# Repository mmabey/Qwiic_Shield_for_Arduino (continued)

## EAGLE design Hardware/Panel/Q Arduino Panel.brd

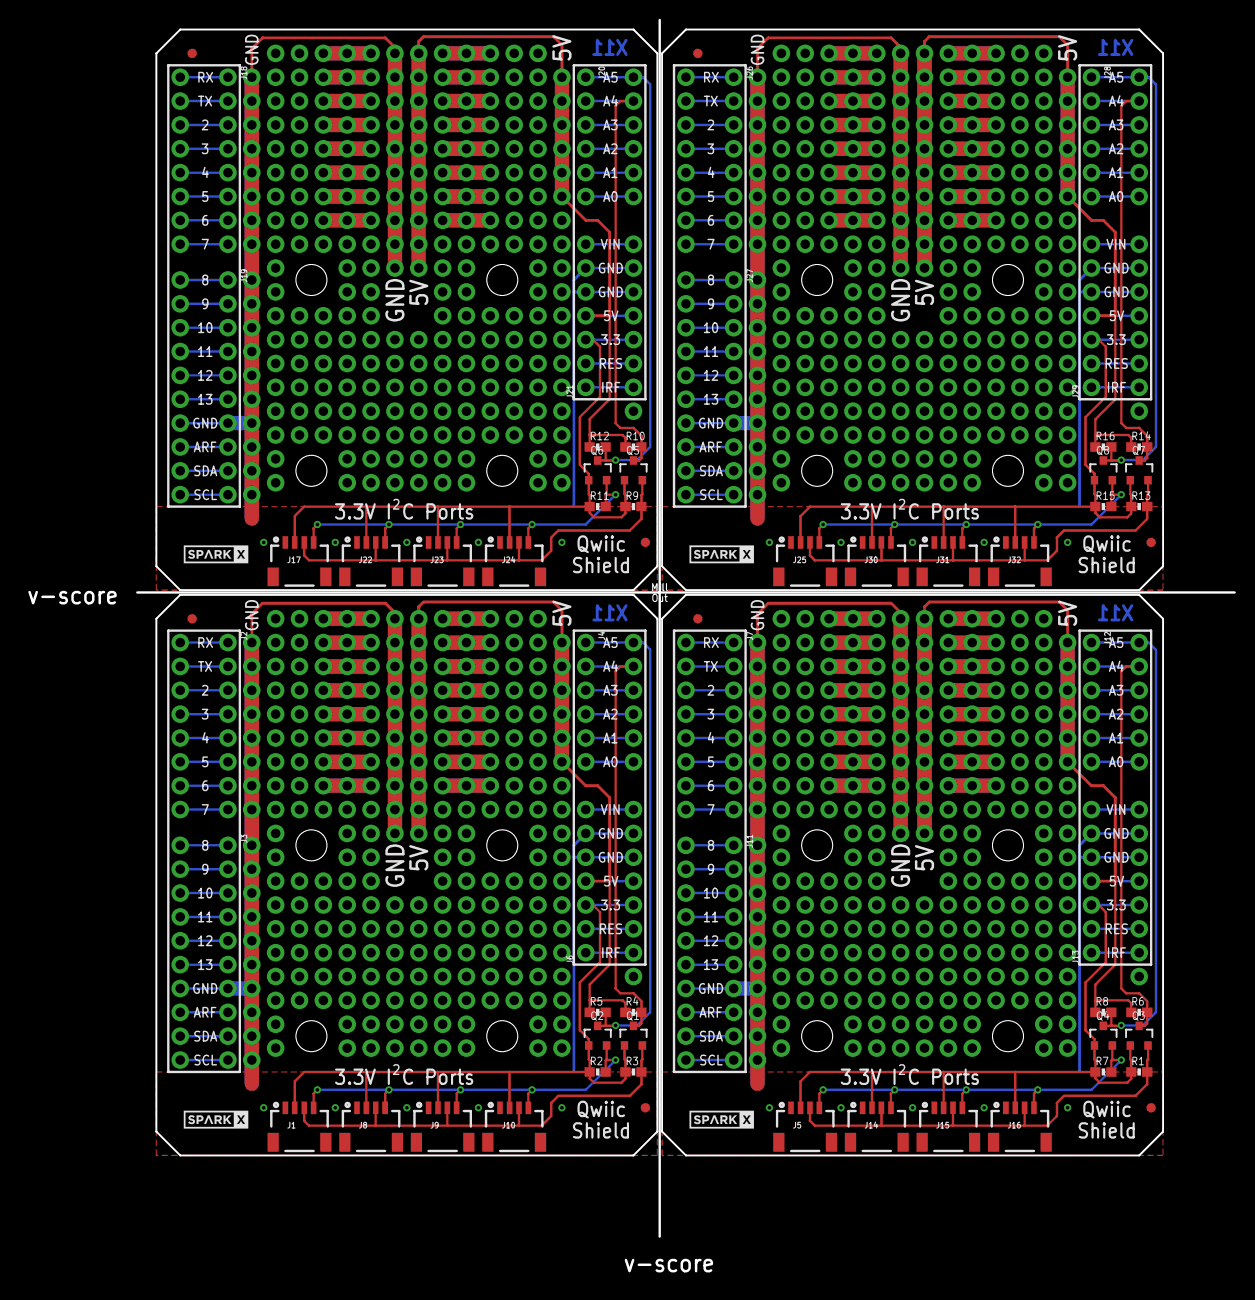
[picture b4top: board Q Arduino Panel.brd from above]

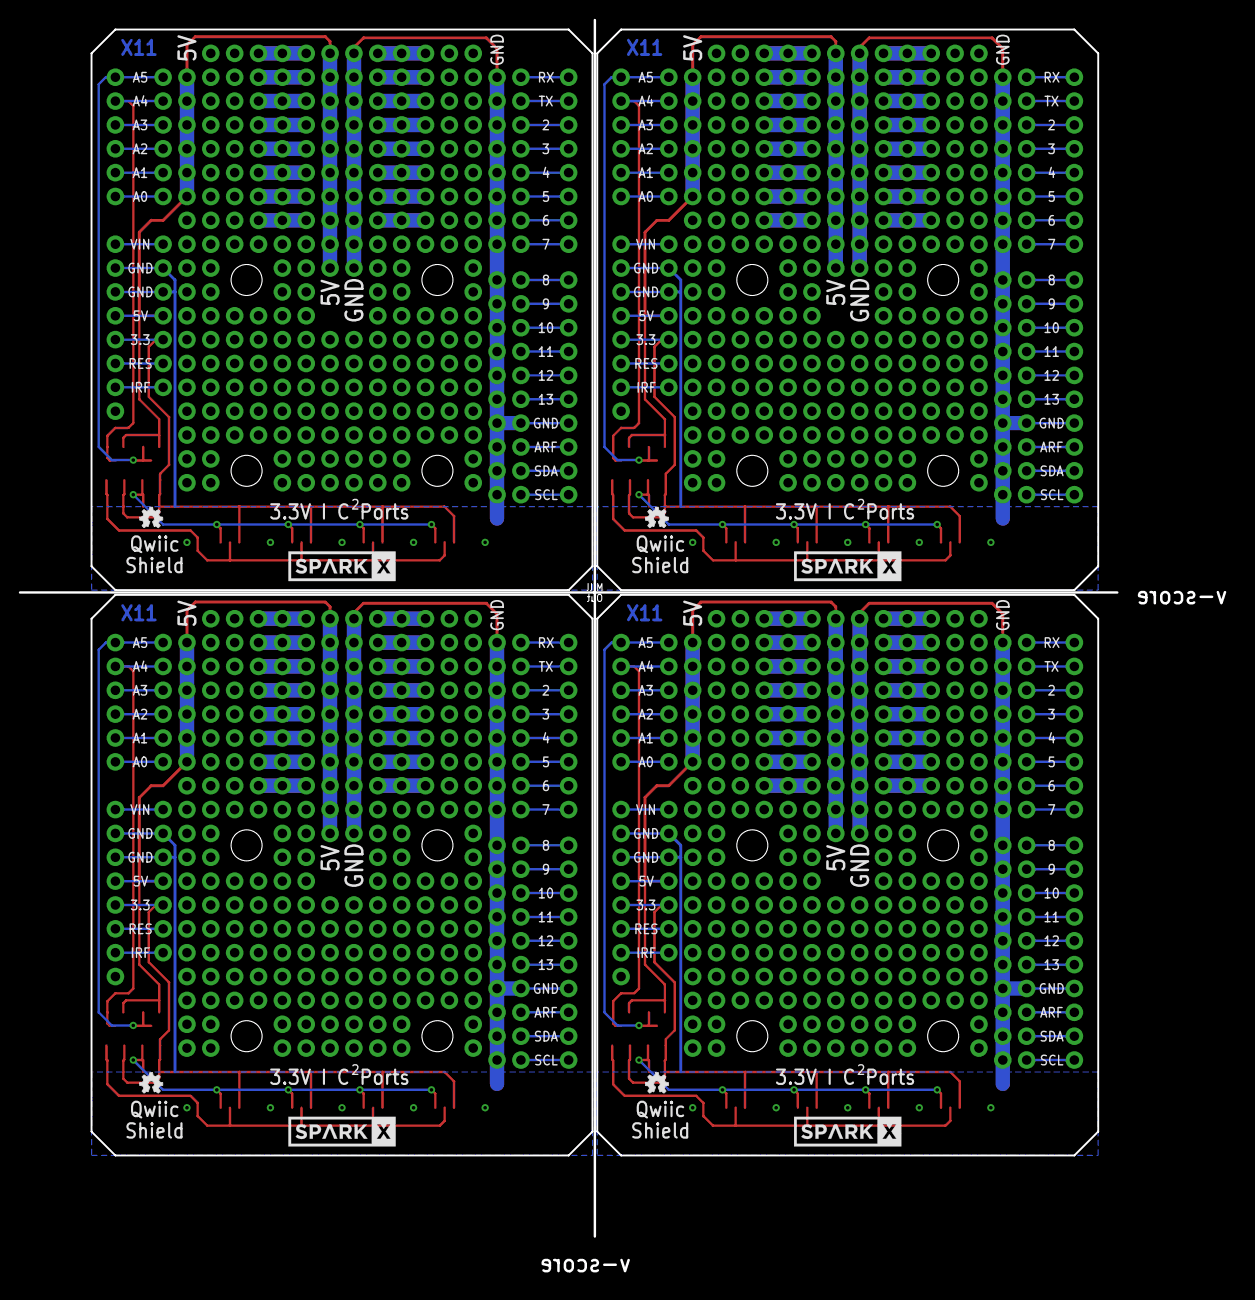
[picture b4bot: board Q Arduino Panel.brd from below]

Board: 2 copper layers, 116.8 x 129.5 mm, 84 parts (8 on the bottom side), 124 nets.

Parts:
FD1, FD2, FD3, FD4, FD5, FD6, FD7, FD8: FIDUCIAL1X2; FIDUCIAL-1X2
J1, J5, J8, J9, J10, J14, J15, J16, J17, J22, J23, J24, J25, J30, J31, J32: 1X04_1MM_RA
J2, J7, J18, J26: 1X08_NO_SILK
J3, J11, J19, J27: 1X10_NO_SILK
J4, J12, J20, J28: 1X06_NO_SILK
J6, J13, J21, J29: 1X07_NO_SILK
LOGO1, LOGO2, LOGO3, LOGO4: OSHW-LOGOMINI; OSHW-LOGO-MINI
Q1, Q2, Q3, Q4, Q5, Q6, Q7, Q8: 200mA/50V; SOT23-3
R1, R2, R3, R4, R5, R6, R7, R8, R9, R10, R11, R12, R13, R14, R15, R16: 4.7K; 0603-RES
U1, U2, U3, U4: ARDUINO UNO; UNO_R3_SHIELD_NOLABELS
U$1, U$4, U$7, U$10: SPARKX-LOGO3; SPARKX-SMALL
U$2, U$5, U$8, U$11: SPARKX-LOGO5; SPARKX-LARGE
U$3, U$6, U$9, U$12: QWIIC_BOARD_OUTLINEH; QWIIC_BOARD_MOUNT_HOLES

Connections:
3.3V: J1.2, J6.3, J8.2, J9.2, J10.2, Q1.1, Q2.1, R2.1, R3.1, U1.3.3V
3.3V1: J5.2, J13.3, J14.2, J15.2, J16.2, Q3.1, Q4.1, R1.1, R7.1, U2.3.3V
3.3V2: J17.2, J21.3, J22.2, J23.2, J24.2, Q5.1, Q6.1, R9.1, R11.1, U3.3.3V
3.3V3: J25.2, J29.3, J30.2, J31.2, J32.2, Q7.1, Q8.1, R13.1, R15.1, U4.3.3V
5V: J6.4, R4.1, R5.1, U1.5V
5V1: J13.4, R6.1, R8.1, U2.5V
5V2: J21.4, R10.1, R12.1, U3.5V
5V3: J29.4, R14.1, R16.1, U4.5V
A0: J4.6, U1.A0
A1: J4.5, U1.A1
A2: J4.4, U1.A2
A3: J4.3, U1.A3
A4: J12.3, U2.A3
A5: J12.4, U2.A2
A6: J12.5, U2.A1
A7: J12.6, U2.A0
A8: J20.3, U3.A3
A9: J20.4, U3.A2
A10: J20.5, U3.A1
A11: J20.6, U3.A0
A12: J28.3, U4.A3
A13: J28.4, U4.A2
A14: J28.5, U4.A1
A15: J28.6, U4.A0
AREF: J3.8, U1.AREF
AREF1: J11.8, U2.AREF
AREF2: J19.8, U3.AREF
AREF3: J27.8, U4.AREF
D1: J7.3, U2.D2
D2: J2.3, U1.D2
D3: J2.4, U1.D3
D4: J2.5, U1.D4
D5: J2.6, U1.D5
D6: J2.7, U1.D6
D7: J2.8, U1.D7
D8: J3.1, U1.D8
D9: J3.2, U1.D9
D10: J3.3, U1.D10
D11: J3.4, U1.D11
D12: J3.5, U1.D12
D13: J3.6, U1.D13
D14: J7.4, U2.D3
D15: J7.5, U2.D4
D16: J7.6, U2.D5
D17: J7.7, U2.D6
D18: J7.8, U2.D7
D19: J11.1, U2.D8
D20: J11.2, U2.D9
D21: J11.3, U2.D10
D22: J11.4, U2.D11
D23: J11.5, U2.D12
D24: J11.6, U2.D13
D25: J18.3, U3.D2
D26: J18.4, U3.D3
D27: J18.5, U3.D4
D28: J18.6, U3.D5
D29: J18.7, U3.D6
D30: J18.8, U3.D7
D31: J19.1, U3.D8
D32: J19.2, U3.D9
D33: J19.3, U3.D10
D34: J19.4, U3.D11
D35: J19.5, U3.D12
D36: J19.6, U3.D13
D37: J26.3, U4.D2
D38: J26.4, U4.D3
D39: J26.5, U4.D4
D40: J26.6, U4.D5
D41: J26.7, U4.D6
D42: J26.8, U4.D7
D43: J27.1, U4.D8
D44: J27.2, U4.D9
D45: J27.3, U4.D10
D46: J27.4, U4.D11
D47: J27.5, U4.D12
D48: J27.6, U4.D13
GND: J1.1, J3.7, J6.5, J6.6, J8.1, J9.1, J10.1, U1.GND@0, U1.GND@1, U1.GND@2
GND1: J5.1, J11.7, J13.5, J13.6, J14.1, J15.1, J16.1, U2.GND@0, U2.GND@1, U2.GND@2
GND2: J17.1, J19.7, J21.5, J21.6, J22.1, J23.1, J24.1, U3.GND@0, U3.GND@1, U3.GND@2
GND3: J25.1, J27.7, J29.5, J29.6, J30.1, J31.1, J32.1, U4.GND@0, U4.GND@1, U4.GND@2
HV_SCL: J4.1, Q2.3, R5.2, U1.A5
HV_SCL1: J12.1, Q4.3, R8.2, U2.A5
HV_SCL2: J20.1, Q6.3, R12.2, U3.A5
HV_SCL3: J28.1, Q8.3, R16.2, U4.A5
HV_SDA: J4.2, Q1.3, R4.2, U1.A4
HV_SDA1: J12.2, Q3.3, R6.2, U2.A4
HV_SDA2: J20.2, Q5.3, R10.2, U3.A4
HV_SDA3: J28.2, Q7.3, R14.2, U4.A4
IOREF: J6.1, U1.IOREF
IOREF1: J13.1, U2.IOREF
IOREF2: J21.1, U3.IOREF
IOREF3: J29.1, U4.IOREF
RES: J6.2, U1.RES
RES1: J13.2, U2.RES
RES2: J21.2, U3.RES
RES3: J29.2, U4.RES
RX: J2.1, U1.RX
RX1: J7.1, U2.RX
RX2: J18.1, U3.RX
RX3: J26.1, U4.RX
SCL: J1.4, J8.4, J9.4, J10.4, Q2.2, R2.2
SCL1: J3.10, U1.SCL
SCL2: J5.4, J14.4, J15.4, J16.4, Q4.2, R7.2
SCL3: J11.10, U2.SCL
SCL4: J17.4, J22.4, J23.4, J24.4, Q6.2, R11.2
SCL5: J19.10, U3.SCL
SCL6: J25.4, J30.4, J31.4, J32.4, Q8.2, R15.2
SCL7: J27.10, U4.SCL
SDA: J1.3, J8.3, J9.3, J10.3, Q1.2, R3.2
SDA1: J3.9, U1.SDA
SDA2: J5.3, J14.3, J15.3, J16.3, Q3.2, R1.2
SDA3: J11.9, U2.SDA
SDA4: J17.3, J22.3, J23.3, J24.3, Q5.2, R9.2
SDA5: J19.9, U3.SDA
SDA6: J25.3, J30.3, J31.3, J32.3, Q7.2, R13.2
SDA7: J27.9, U4.SDA
TX: J2.2, U1.TX
TX1: J7.2, U2.TX
TX2: J18.2, U3.TX
TX3: J26.2, U4.TX
VIN: J6.7, U1.VIN
VIN1: J13.7, U2.VIN
VIN2: J21.7, U3.VIN
VIN3: J29.7, U4.VIN

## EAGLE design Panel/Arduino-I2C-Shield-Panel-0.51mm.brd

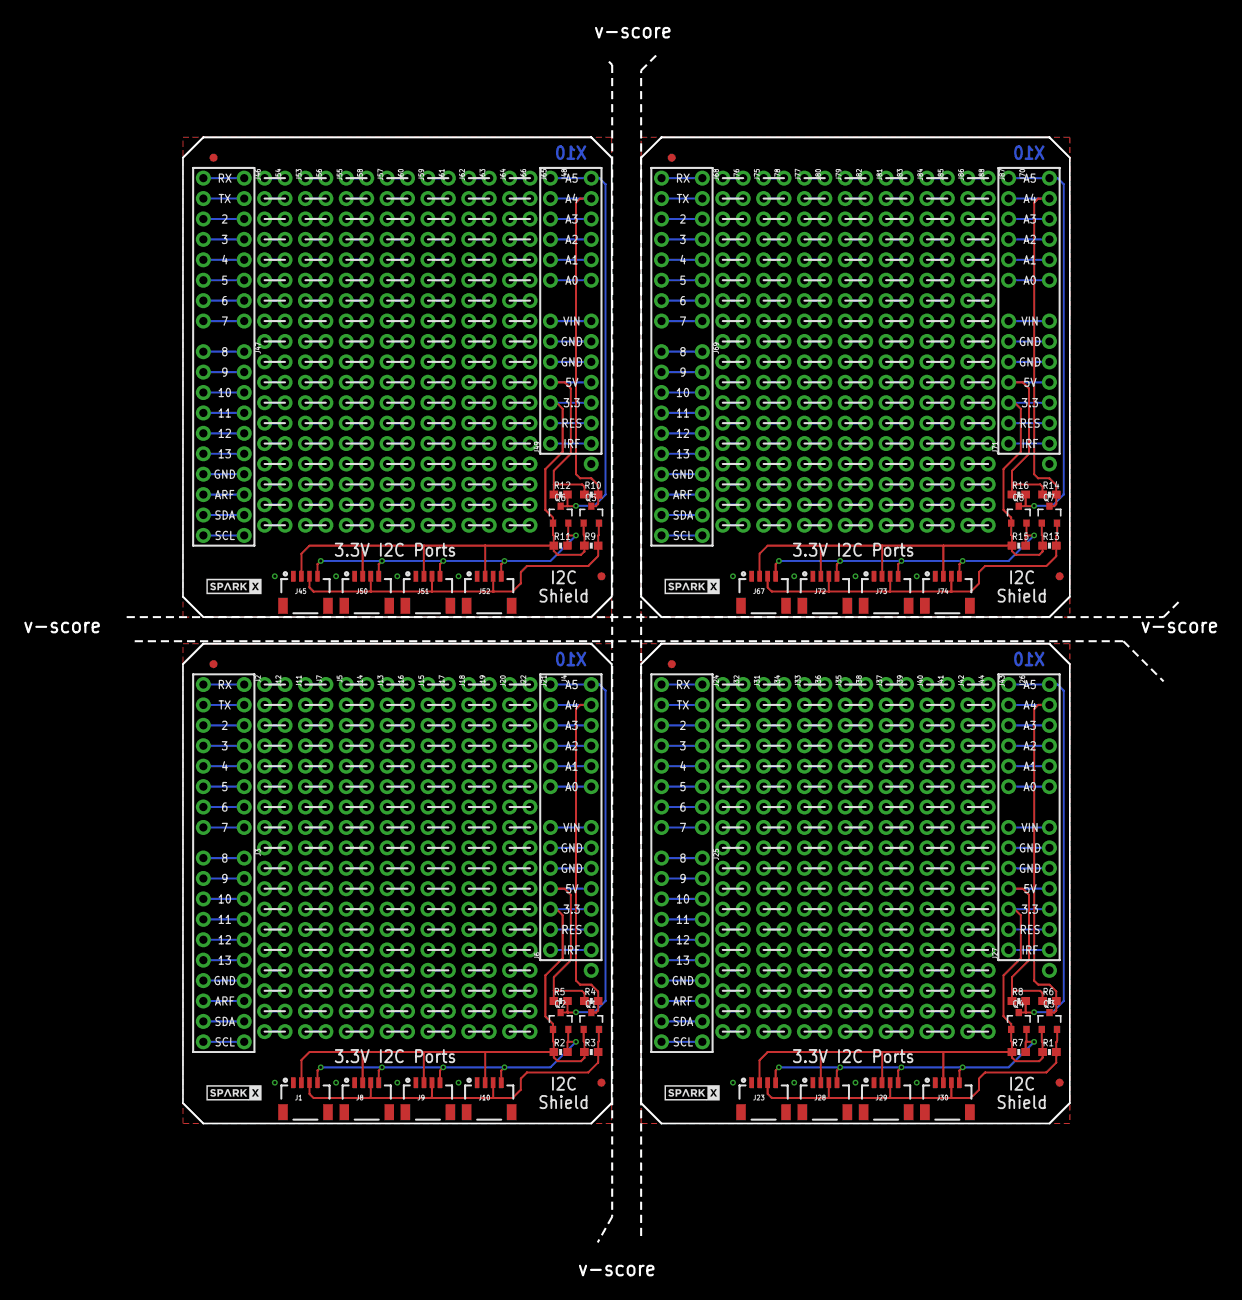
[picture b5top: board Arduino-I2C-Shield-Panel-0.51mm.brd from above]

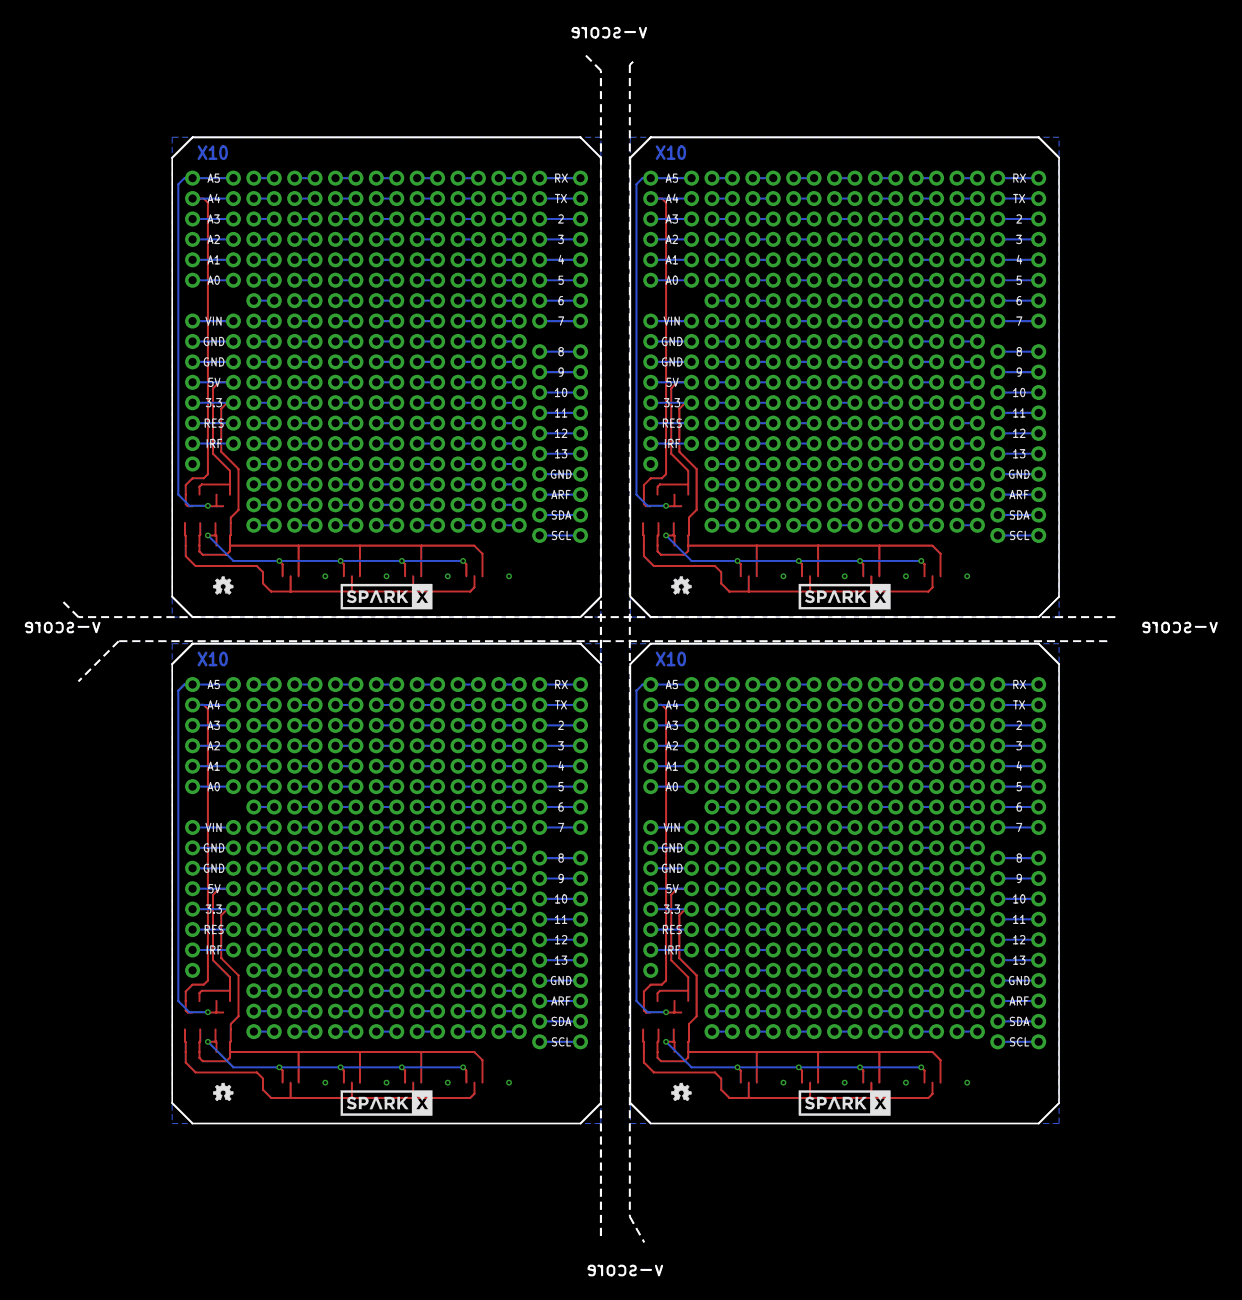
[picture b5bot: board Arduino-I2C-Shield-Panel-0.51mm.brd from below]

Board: 2 copper layers, 131.0 x 147.8 mm, 136 parts (8 on the bottom side), 628 nets.

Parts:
FD1, FD2, FD3, FD4, FD5, FD6, FD7, FD8: FIDUCIAL1X2; FIDUCIAL-1X2
J1, J8, J9, J10, J23, J28, J29, J30, J45, J50, J51, J52, J67, J72, J73, J74: 1X04_1MM_RA
J2, J24, J46, J68: 1X08_NO_SILK
J3, J25, J47, J69: 1X10_NO_SILK
J4, J26, J48, J70: 1X06_NO_SILK
J5, J7, J11, J12, J13, J14, J15, J16, J17, J18, J19, J20, J21, J22, J31, J32, J33, J34, J35, J36, J37, J38, J39, J40, J41, J42, J43, J44, J53, J54, J55, J56, J57, J58, J59, J60, J61, J62, J63, J64, J65, J66, J75, J76, J77, J78, J79, J80, J81, J82, J83, J84, J85, J86, J87, J88: 1X18_NO_SILK
J6, J27, J49, J71: 1X07_NO_SILK
LOGO1, LOGO2, LOGO3, LOGO4: OSHW-LOGOMINI; OSHW-LOGO-MINI
Q1, Q2, Q3, Q4, Q5, Q6, Q7, Q8: 200mA/50V; SOT23-3
R1, R2, R3, R4, R5, R6, R7, R8, R9, R10, R11, R12, R13, R14, R15, R16: 4.7K; 0603-RES
U1, U2, U3, U4: ARDUINO UNO; UNO_R3_SHIELD_NOLABELS
U$1, U$3, U$5, U$7: SPARKX-LOGO3; SPARKX-SMALL
U$2, U$4, U$6, U$8: SPARKX-LOGO5; SPARKX-LARGE

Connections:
3.3V: J1.2, J6.3, J8.2, J9.2, J10.2, Q1.1, Q2.1, R2.1, R3.1, U1.3.3V
3.3V1: J23.2, J27.3, J28.2, J29.2, J30.2, Q3.1, Q4.1, R1.1, R7.1, U2.3.3V
3.3V2: J45.2, J49.3, J50.2, J51.2, J52.2, Q5.1, Q6.1, R9.1, R11.1, U3.3.3V
3.3V3: J67.2, J71.3, J72.2, J73.2, J74.2, Q7.1, Q8.1, R13.1, R15.1, U4.3.3V
5V: J6.4, R4.1, R5.1, U1.5V
5V1: J27.4, R6.1, R8.1, U2.5V
5V2: J49.4, R10.1, R12.1, U3.5V
5V3: J71.4, R14.1, R16.1, U4.5V
A0: J4.6, U1.A0
A1: J4.5, U1.A1
A2: J4.4, U1.A2
A3: J4.3, U1.A3
A4: J26.3, U2.A3
A5: J26.4, U2.A2
A6: J26.5, U2.A1
A7: J26.6, U2.A0
A8: J48.3, U3.A3
A9: J48.4, U3.A2
A10: J48.5, U3.A1
A11: J48.6, U3.A0
A12: J70.3, U4.A3
A13: J70.4, U4.A2
A14: J70.5, U4.A1
A15: J70.6, U4.A0
AREF: J3.8, U1.AREF
AREF1: J25.8, U2.AREF
AREF2: J47.8, U3.AREF
AREF3: J69.8, U4.AREF
D1: J24.3, U2.D2
D2: J2.3, U1.D2
D3: J2.4, U1.D3
D4: J2.5, U1.D4
D5: J2.6, U1.D5
D6: J2.7, U1.D6
D7: J2.8, U1.D7
D8: J3.1, U1.D8
D9: J3.2, U1.D9
D10: J3.3, U1.D10
D11: J3.4, U1.D11
D12: J3.5, U1.D12
D13: J3.6, U1.D13
D14: J24.4, U2.D3
D15: J24.5, U2.D4
D16: J24.6, U2.D5
D17: J24.7, U2.D6
D18: J24.8, U2.D7
D19: J25.1, U2.D8
D20: J25.2, U2.D9
D21: J25.3, U2.D10
D22: J25.4, U2.D11
D23: J25.5, U2.D12
D24: J25.6, U2.D13
D25: J46.3, U3.D2
D26: J46.4, U3.D3
D27: J46.5, U3.D4
D28: J46.6, U3.D5
D29: J46.7, U3.D6
D30: J46.8, U3.D7
D31: J47.1, U3.D8
D32: J47.2, U3.D9
D33: J47.3, U3.D10
D34: J47.4, U3.D11
D35: J47.5, U3.D12
D36: J47.6, U3.D13
D37: J68.3, U4.D2
D38: J68.4, U4.D3
D39: J68.5, U4.D4
D40: J68.6, U4.D5
D41: J68.7, U4.D6
D42: J68.8, U4.D7
D43: J69.1, U4.D8
D44: J69.2, U4.D9
D45: J69.3, U4.D10
D46: J69.4, U4.D11
D47: J69.5, U4.D12
D48: J69.6, U4.D13
GND: J1.1, J3.7, J6.5, J6.6, J8.1, J9.1, J10.1, U1.GND@0, U1.GND@1, U1.GND@2
GND1: J23.1, J25.7, J27.5, J27.6, J28.1, J29.1, J30.1, U2.GND@0, U2.GND@1, U2.GND@2
GND2: J45.1, J47.7, J49.5, J49.6, J50.1, J51.1, J52.1, U3.GND@0, U3.GND@1, U3.GND@2
GND3: J67.1, J69.7, J71.5, J71.6, J72.1, J73.1, J74.1, U4.GND@0, U4.GND@1, U4.GND@2
HV_SCL: J4.1, Q2.3, R5.2, U1.A5
HV_SCL1: J26.1, Q4.3, R8.2, U2.A5
HV_SCL2: J48.1, Q6.3, R12.2, U3.A5
HV_SCL3: J70.1, Q8.3, R16.2, U4.A5
HV_SDA: J4.2, Q1.3, R4.2, U1.A4
HV_SDA1: J26.2, Q3.3, R6.2, U2.A4
HV_SDA2: J48.2, Q5.3, R10.2, U3.A4
HV_SDA3: J70.2, Q7.3, R14.2, U4.A4
IOREF: J6.1, U1.IOREF
IOREF1: J27.1, U2.IOREF
IOREF2: J49.1, U3.IOREF
IOREF3: J71.1, U4.IOREF
unnamed: J5.2, J7.2
unnamed: J5.3, J7.3
unnamed: J5.4, J7.4
unnamed: J5.5, J7.5
unnamed: J5.6, J7.6
unnamed: J5.7, J7.7
unnamed: J5.8, J7.8
unnamed: J5.9, J7.9
unnamed: J5.10, J7.10
unnamed: J5.11, J7.11
unnamed: J5.12, J7.12
unnamed: J5.13, J7.13
unnamed: J5.14, J7.14
unnamed: J5.15, J7.15
unnamed: J5.16, J7.16
unnamed: J5.17, J7.17
unnamed: J5.18, J7.18
unnamed: J5.1, J7.1
unnamed: J13.2, J14.2
unnamed: J13.3, J14.3
unnamed: J11.2, J12.2
unnamed: J11.3, J12.3
unnamed: J11.4, J12.4
unnamed: J11.5, J12.5
unnamed: J11.6, J12.6
unnamed: J11.7, J12.7
unnamed: J11.8, J12.8
unnamed: J11.9, J12.9
unnamed: J11.10, J12.10
unnamed: J11.11, J12.11
unnamed: J11.12, J12.12
unnamed: J11.13, J12.13
unnamed: J11.14, J12.14
unnamed: J11.15, J12.15
unnamed: J11.16, J12.16
unnamed: J11.17, J12.17
unnamed: J11.18, J12.18
unnamed: J11.1, J12.1
unnamed: J13.4, J14.4
unnamed: J13.5, J14.5
unnamed: J13.6, J14.6
unnamed: J13.7, J14.7
unnamed: J13.8, J14.8
unnamed: J13.9, J14.9
unnamed: J13.10, J14.10
unnamed: J13.11, J14.11
unnamed: J13.12, J14.12
unnamed: J13.13, J14.13
unnamed: J13.14, J14.14
unnamed: J13.15, J14.15
unnamed: J13.16, J14.16
unnamed: J13.17, J14.17
unnamed: J13.18, J14.18
unnamed: J13.1, J14.1
unnamed: J15.2, J16.2
unnamed: J15.3, J16.3
unnamed: J15.4, J16.4
unnamed: J15.5, J16.5
unnamed: J15.6, J16.6
unnamed: J15.7, J16.7
unnamed: J15.8, J16.8
unnamed: J15.9, J16.9
unnamed: J15.10, J16.10
unnamed: J15.11, J16.11
unnamed: J15.12, J16.12
unnamed: J15.13, J16.13
unnamed: J15.14, J16.14
unnamed: J15.15, J16.15
unnamed: J15.16, J16.16
unnamed: J15.17, J16.17
unnamed: J15.18, J16.18
unnamed: J15.1, J16.1
unnamed: J17.2, J18.2
unnamed: J17.3, J18.3
unnamed: J17.4, J18.4
unnamed: J17.5, J18.5
unnamed: J17.6, J18.6
unnamed: J17.7, J18.7
unnamed: J17.8, J18.8
unnamed: J17.9, J18.9
unnamed: J17.10, J18.10
unnamed: J17.11, J18.11
unnamed: J17.12, J18.12
unnamed: J17.13, J18.13
unnamed: J17.14, J18.14
unnamed: J17.15, J18.15
unnamed: J17.16, J18.16
unnamed: J17.17, J18.17
unnamed: J17.18, J18.18
unnamed: J17.1, J18.1
unnamed: J19.2, J20.2
unnamed: J19.3, J20.3
unnamed: J19.4, J20.4
unnamed: J19.5, J20.5
unnamed: J19.6, J20.6
unnamed: J19.7, J20.7
unnamed: J19.8, J20.8
unnamed: J19.9, J20.9
unnamed: J19.10, J20.10
unnamed: J19.11, J20.11
unnamed: J19.12, J20.12
unnamed: J19.13, J20.13
unnamed: J19.14, J20.14
unnamed: J19.15, J20.15
unnamed: J19.16, J20.16
unnamed: J19.17, J20.17
unnamed: J19.18, J20.18
unnamed: J19.1, J20.1
unnamed: J21.2, J22.2
unnamed: J21.3, J22.3
unnamed: J21.4, J22.4
unnamed: J21.5, J22.5
unnamed: J21.6, J22.6
unnamed: J21.7, J22.7
unnamed: J21.8, J22.8
unnamed: J21.9, J22.9
unnamed: J21.10, J22.10
unnamed: J21.11, J22.11
unnamed: J21.12, J22.12
unnamed: J21.13, J22.13
unnamed: J21.14, J22.14
unnamed: J21.15, J22.15
unnamed: J21.16, J22.16
unnamed: J21.17, J22.17
unnamed: J21.18, J22.18
unnamed: J21.1, J22.1
unnamed: J31.2, J32.2
unnamed: J31.3, J32.3
unnamed: J31.4, J32.4
unnamed: J31.5, J32.5
unnamed: J31.6, J32.6
unnamed: J31.7, J32.7
unnamed: J31.8, J32.8
unnamed: J31.9, J32.9
unnamed: J31.10, J32.10
unnamed: J31.11, J32.11
unnamed: J31.12, J32.12
unnamed: J31.13, J32.13
unnamed: J31.14, J32.14
unnamed: J31.15, J32.15
unnamed: J31.16, J32.16
unnamed: J31.17, J32.17
unnamed: J31.18, J32.18
unnamed: J31.1, J32.1
unnamed: J33.2, J34.2
unnamed: J33.3, J34.3
unnamed: J33.4, J34.4
unnamed: J33.5, J34.5
unnamed: J33.6, J34.6
unnamed: J33.7, J34.7
unnamed: J33.8, J34.8
unnamed: J33.9, J34.9
unnamed: J33.10, J34.10
unnamed: J33.11, J34.11
unnamed: J33.12, J34.12
unnamed: J33.13, J34.13
unnamed: J33.14, J34.14
unnamed: J33.15, J34.15
unnamed: J33.16, J34.16
unnamed: J33.17, J34.17
unnamed: J33.18, J34.18
unnamed: J33.1, J34.1
unnamed: J35.2, J36.2
unnamed: J35.3, J36.3
unnamed: J35.4, J36.4
unnamed: J35.5, J36.5
unnamed: J35.6, J36.6
unnamed: J35.7, J36.7
unnamed: J35.8, J36.8
unnamed: J35.9, J36.9
unnamed: J35.10, J36.10
unnamed: J35.11, J36.11
unnamed: J35.12, J36.12
unnamed: J35.13, J36.13
unnamed: J35.14, J36.14
unnamed: J35.15, J36.15
unnamed: J35.16, J36.16
unnamed: J35.17, J36.17
unnamed: J35.18, J36.18
unnamed: J35.1, J36.1
unnamed: J37.2, J38.2
unnamed: J37.3, J38.3
unnamed: J37.4, J38.4
unnamed: J37.5, J38.5
unnamed: J37.6, J38.6
unnamed: J37.7, J38.7
unnamed: J37.8, J38.8
unnamed: J37.9, J38.9
unnamed: J37.10, J38.10
unnamed: J37.11, J38.11
unnamed: J37.12, J38.12
unnamed: J37.13, J38.13
unnamed: J37.14, J38.14
unnamed: J37.15, J38.15
unnamed: J37.16, J38.16
unnamed: J37.17, J38.17
unnamed: J37.18, J38.18
unnamed: J37.1, J38.1
unnamed: J39.2, J40.2
unnamed: J39.3, J40.3
unnamed: J39.4, J40.4
unnamed: J39.5, J40.5
unnamed: J39.6, J40.6
unnamed: J39.7, J40.7
unnamed: J39.8, J40.8
unnamed: J39.9, J40.9
unnamed: J39.10, J40.10
unnamed: J39.11, J40.11
unnamed: J39.12, J40.12
unnamed: J39.13, J40.13
unnamed: J39.14, J40.14
unnamed: J39.15, J40.15
unnamed: J39.16, J40.16
unnamed: J39.17, J40.17
unnamed: J39.18, J40.18
unnamed: J39.1, J40.1
unnamed: J41.2, J42.2
unnamed: J41.3, J42.3
unnamed: J41.4, J42.4
unnamed: J41.5, J42.5
unnamed: J41.6, J42.6
unnamed: J41.7, J42.7
unnamed: J41.8, J42.8
unnamed: J41.9, J42.9
unnamed: J41.10, J42.10
unnamed: J41.11, J42.11
unnamed: J41.12, J42.12
unnamed: J41.13, J42.13
unnamed: J41.14, J42.14
unnamed: J41.15, J42.15
unnamed: J41.16, J42.16
unnamed: J41.17, J42.17
unnamed: J41.18, J42.18
unnamed: J41.1, J42.1
unnamed: J43.2, J44.2
unnamed: J43.3, J44.3
unnamed: J43.4, J44.4
unnamed: J43.5, J44.5
unnamed: J43.6, J44.6
unnamed: J43.7, J44.7
unnamed: J43.8, J44.8
unnamed: J43.9, J44.9
unnamed: J43.10, J44.10
unnamed: J43.11, J44.11
unnamed: J43.12, J44.12
unnamed: J43.13, J44.13
unnamed: J43.14, J44.14
unnamed: J43.15, J44.15
unnamed: J43.16, J44.16
unnamed: J43.17, J44.17
unnamed: J43.18, J44.18
unnamed: J43.1, J44.1
unnamed: J53.2, J54.2
unnamed: J53.3, J54.3
unnamed: J53.4, J54.4
unnamed: J53.5, J54.5
unnamed: J53.6, J54.6
unnamed: J53.7, J54.7
unnamed: J53.8, J54.8
unnamed: J53.9, J54.9
unnamed: J53.10, J54.10
unnamed: J53.11, J54.11
unnamed: J53.12, J54.12
unnamed: J53.13, J54.13
unnamed: J53.14, J54.14
unnamed: J53.15, J54.15
unnamed: J53.16, J54.16
unnamed: J53.17, J54.17
unnamed: J53.18, J54.18
unnamed: J53.1, J54.1
unnamed: J55.2, J56.2
unnamed: J55.3, J56.3
unnamed: J55.4, J56.4
unnamed: J55.5, J56.5
unnamed: J55.6, J56.6
unnamed: J55.7, J56.7
unnamed: J55.8, J56.8
unnamed: J55.9, J56.9
unnamed: J55.10, J56.10
unnamed: J55.11, J56.11
unnamed: J55.12, J56.12
unnamed: J55.13, J56.13
unnamed: J55.14, J56.14
unnamed: J55.15, J56.15
unnamed: J55.16, J56.16
unnamed: J55.17, J56.17
unnamed: J55.18, J56.18
unnamed: J55.1, J56.1
unnamed: J57.2, J58.2
unnamed: J57.3, J58.3
unnamed: J57.4, J58.4
unnamed: J57.5, J58.5
unnamed: J57.6, J58.6
unnamed: J57.7, J58.7
unnamed: J57.8, J58.8
unnamed: J57.9, J58.9
unnamed: J57.10, J58.10
unnamed: J57.11, J58.11
unnamed: J57.12, J58.12
unnamed: J57.13, J58.13
unnamed: J57.14, J58.14
unnamed: J57.15, J58.15
unnamed: J57.16, J58.16
unnamed: J57.17, J58.17
unnamed: J57.18, J58.18
unnamed: J57.1, J58.1
unnamed: J59.2, J60.2
unnamed: J59.3, J60.3
unnamed: J59.4, J60.4
unnamed: J59.5, J60.5
unnamed: J59.6, J60.6
unnamed: J59.7, J60.7
unnamed: J59.8, J60.8
unnamed: J59.9, J60.9
unnamed: J59.10, J60.10
unnamed: J59.11, J60.11
unnamed: J59.12, J60.12
unnamed: J59.13, J60.13
unnamed: J59.14, J60.14
unnamed: J59.15, J60.15
unnamed: J59.16, J60.16
unnamed: J59.17, J60.17
unnamed: J59.18, J60.18
unnamed: J59.1, J60.1
unnamed: J61.2, J62.2
unnamed: J61.3, J62.3
unnamed: J61.4, J62.4
unnamed: J61.5, J62.5
unnamed: J61.6, J62.6
unnamed: J61.7, J62.7
unnamed: J61.8, J62.8
unnamed: J61.9, J62.9
unnamed: J61.10, J62.10
unnamed: J61.11, J62.11
unnamed: J61.12, J62.12
unnamed: J61.13, J62.13
unnamed: J61.14, J62.14
unnamed: J61.15, J62.15
unnamed: J61.16, J62.16
unnamed: J61.17, J62.17
unnamed: J61.18, J62.18
unnamed: J61.1, J62.1
unnamed: J63.2, J64.2
unnamed: J63.3, J64.3
unnamed: J63.4, J64.4
unnamed: J63.5, J64.5
unnamed: J63.6, J64.6
unnamed: J63.7, J64.7
unnamed: J63.8, J64.8
unnamed: J63.9, J64.9
unnamed: J63.10, J64.10
unnamed: J63.11, J64.11
unnamed: J63.12, J64.12
unnamed: J63.13, J64.13
unnamed: J63.14, J64.14
unnamed: J63.15, J64.15
unnamed: J63.16, J64.16
unnamed: J63.17, J64.17
unnamed: J63.18, J64.18
unnamed: J63.1, J64.1
unnamed: J65.2, J66.2
unnamed: J65.3, J66.3
unnamed: J65.4, J66.4
unnamed: J65.5, J66.5
unnamed: J65.6, J66.6
unnamed: J65.7, J66.7
unnamed: J65.8, J66.8
unnamed: J65.9, J66.9
unnamed: J65.10, J66.10
unnamed: J65.11, J66.11
unnamed: J65.12, J66.12
unnamed: J65.13, J66.13
unnamed: J65.14, J66.14
unnamed: J65.15, J66.15
unnamed: J65.16, J66.16
unnamed: J65.17, J66.17
unnamed: J65.18, J66.18
unnamed: J65.1, J66.1
unnamed: J75.2, J76.2
unnamed: J75.3, J76.3
unnamed: J75.4, J76.4
unnamed: J75.5, J76.5
unnamed: J75.6, J76.6
unnamed: J75.7, J76.7
unnamed: J75.8, J76.8
unnamed: J75.9, J76.9
unnamed: J75.10, J76.10
unnamed: J75.11, J76.11
unnamed: J75.12, J76.12
unnamed: J75.13, J76.13
unnamed: J75.14, J76.14
unnamed: J75.15, J76.15
unnamed: J75.16, J76.16
unnamed: J75.17, J76.17
unnamed: J75.18, J76.18
unnamed: J75.1, J76.1
unnamed: J77.2, J78.2
unnamed: J77.3, J78.3
unnamed: J77.4, J78.4
unnamed: J77.5, J78.5
unnamed: J77.6, J78.6
unnamed: J77.7, J78.7
unnamed: J77.8, J78.8
unnamed: J77.9, J78.9
unnamed: J77.10, J78.10
unnamed: J77.11, J78.11
unnamed: J77.12, J78.12
unnamed: J77.13, J78.13
unnamed: J77.14, J78.14
unnamed: J77.15, J78.15
unnamed: J77.16, J78.16
unnamed: J77.17, J78.17
unnamed: J77.18, J78.18
unnamed: J77.1, J78.1
unnamed: J79.2, J80.2
unnamed: J79.3, J80.3
unnamed: J79.4, J80.4
unnamed: J79.5, J80.5
unnamed: J79.6, J80.6
unnamed: J79.7, J80.7
unnamed: J79.8, J80.8
unnamed: J79.9, J80.9
unnamed: J79.10, J80.10
unnamed: J79.11, J80.11
unnamed: J79.12, J80.12
unnamed: J79.13, J80.13
unnamed: J79.14, J80.14
unnamed: J79.15, J80.15
unnamed: J79.16, J80.16
unnamed: J79.17, J80.17
unnamed: J79.18, J80.18
unnamed: J79.1, J80.1
unnamed: J81.2, J82.2
unnamed: J81.3, J82.3
unnamed: J81.4, J82.4
unnamed: J81.5, J82.5
unnamed: J81.6, J82.6
unnamed: J81.7, J82.7
unnamed: J81.8, J82.8
unnamed: J81.9, J82.9
unnamed: J81.10, J82.10
unnamed: J81.11, J82.11
unnamed: J81.12, J82.12
unnamed: J81.13, J82.13
unnamed: J81.14, J82.14
unnamed: J81.15, J82.15
unnamed: J81.16, J82.16
unnamed: J81.17, J82.17
unnamed: J81.18, J82.18
unnamed: J81.1, J82.1
unnamed: J83.2, J84.2
unnamed: J83.3, J84.3
unnamed: J83.4, J84.4
unnamed: J83.5, J84.5
unnamed: J83.6, J84.6
unnamed: J83.7, J84.7
unnamed: J83.8, J84.8
unnamed: J83.9, J84.9
unnamed: J83.10, J84.10
unnamed: J83.11, J84.11
unnamed: J83.12, J84.12
unnamed: J83.13, J84.13
unnamed: J83.14, J84.14
unnamed: J83.15, J84.15
unnamed: J83.16, J84.16
unnamed: J83.17, J84.17
unnamed: J83.18, J84.18
unnamed: J83.1, J84.1
unnamed: J85.2, J86.2
unnamed: J85.3, J86.3
unnamed: J85.4, J86.4
unnamed: J85.5, J86.5
unnamed: J85.6, J86.6
unnamed: J85.7, J86.7
unnamed: J85.8, J86.8
unnamed: J85.9, J86.9
unnamed: J85.10, J86.10
unnamed: J85.11, J86.11
unnamed: J85.12, J86.12
unnamed: J85.13, J86.13
unnamed: J85.14, J86.14
unnamed: J85.15, J86.15
unnamed: J85.16, J86.16
unnamed: J85.17, J86.17
unnamed: J85.18, J86.18
unnamed: J85.1, J86.1
unnamed: J87.2, J88.2
unnamed: J87.3, J88.3
unnamed: J87.4, J88.4
unnamed: J87.5, J88.5
unnamed: J87.6, J88.6
unnamed: J87.7, J88.7
unnamed: J87.8, J88.8
unnamed: J87.9, J88.9
unnamed: J87.10, J88.10
unnamed: J87.11, J88.11
unnamed: J87.12, J88.12
unnamed: J87.13, J88.13
unnamed: J87.14, J88.14
unnamed: J87.15, J88.15
unnamed: J87.16, J88.16
unnamed: J87.17, J88.17
unnamed: J87.18, J88.18
unnamed: J87.1, J88.1
RES: J6.2, U1.RES
RES1: J27.2, U2.RES
RES2: J49.2, U3.RES
RES3: J71.2, U4.RES
RX: J2.1, U1.RX
RX1: J24.1, U2.RX
RX2: J46.1, U3.RX
RX3: J68.1, U4.RX
SCL: J1.4, J8.4, J9.4, J10.4, Q2.2, R2.2
SCL1: J3.10, U1.SCL
SCL2: J23.4, J28.4, J29.4, J30.4, Q4.2, R7.2
SCL3: J25.10, U2.SCL
SCL4: J45.4, J50.4, J51.4, J52.4, Q6.2, R11.2
SCL5: J47.10, U3.SCL
SCL6: J67.4, J72.4, J73.4, J74.4, Q8.2, R15.2
SCL7: J69.10, U4.SCL
SDA: J1.3, J8.3, J9.3, J10.3, Q1.2, R3.2
SDA1: J3.9, U1.SDA
SDA2: J23.3, J28.3, J29.3, J30.3, Q3.2, R1.2
SDA3: J25.9, U2.SDA
SDA4: J45.3, J50.3, J51.3, J52.3, Q5.2, R9.2
SDA5: J47.9, U3.SDA
SDA6: J67.3, J72.3, J73.3, J74.3, Q7.2, R13.2
SDA7: J69.9, U4.SDA
TX: J2.2, U1.TX
TX1: J24.2, U2.TX
TX2: J46.2, U3.TX
TX3: J68.2, U4.TX
VIN: J6.7, U1.VIN
VIN1: J27.7, U2.VIN
VIN2: J49.7, U3.VIN
VIN3: J71.7, U4.VIN

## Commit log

2017-03-07 :octocat: Added .gitattributes & .gitignore files
2017-03-07 Initial layout and panel
2017-03-08 Changing panel to 3mm spacing for v-score
2017-03-08 Updating ignore file
2017-03-13 Adding Mux Shield
2017-03-13 Breaking out reset pin
2017-03-24 Cleaning up repo. Adding pdf schematic.
2017-04-03 File rename
2017-04-14 Adding mounting spot for Qwiic boards
2017-04-14 Adding panel
2017-04-17 Adding Qwiic mounting holes to shield
2017-04-20 Update to readme
2017-04-20 Updates to readme
2017-09-17 Updated board/schematic
    Changes are mostly to make the shield compatible with 3.3V logic
    microcontrollers. This means there's no need for the level shifting
    between the shield and the MCU. Also, the power lines are all connected
    to the 3.3V pin instead of 5V.
2017-10-06 Re-routed board to use SCL/SDA instead of A4/A5
    The Metro Express M0 cannot use A4/A5 as SCL/SDA, so the previous
    version of the shield was completely incompatible with the board.
